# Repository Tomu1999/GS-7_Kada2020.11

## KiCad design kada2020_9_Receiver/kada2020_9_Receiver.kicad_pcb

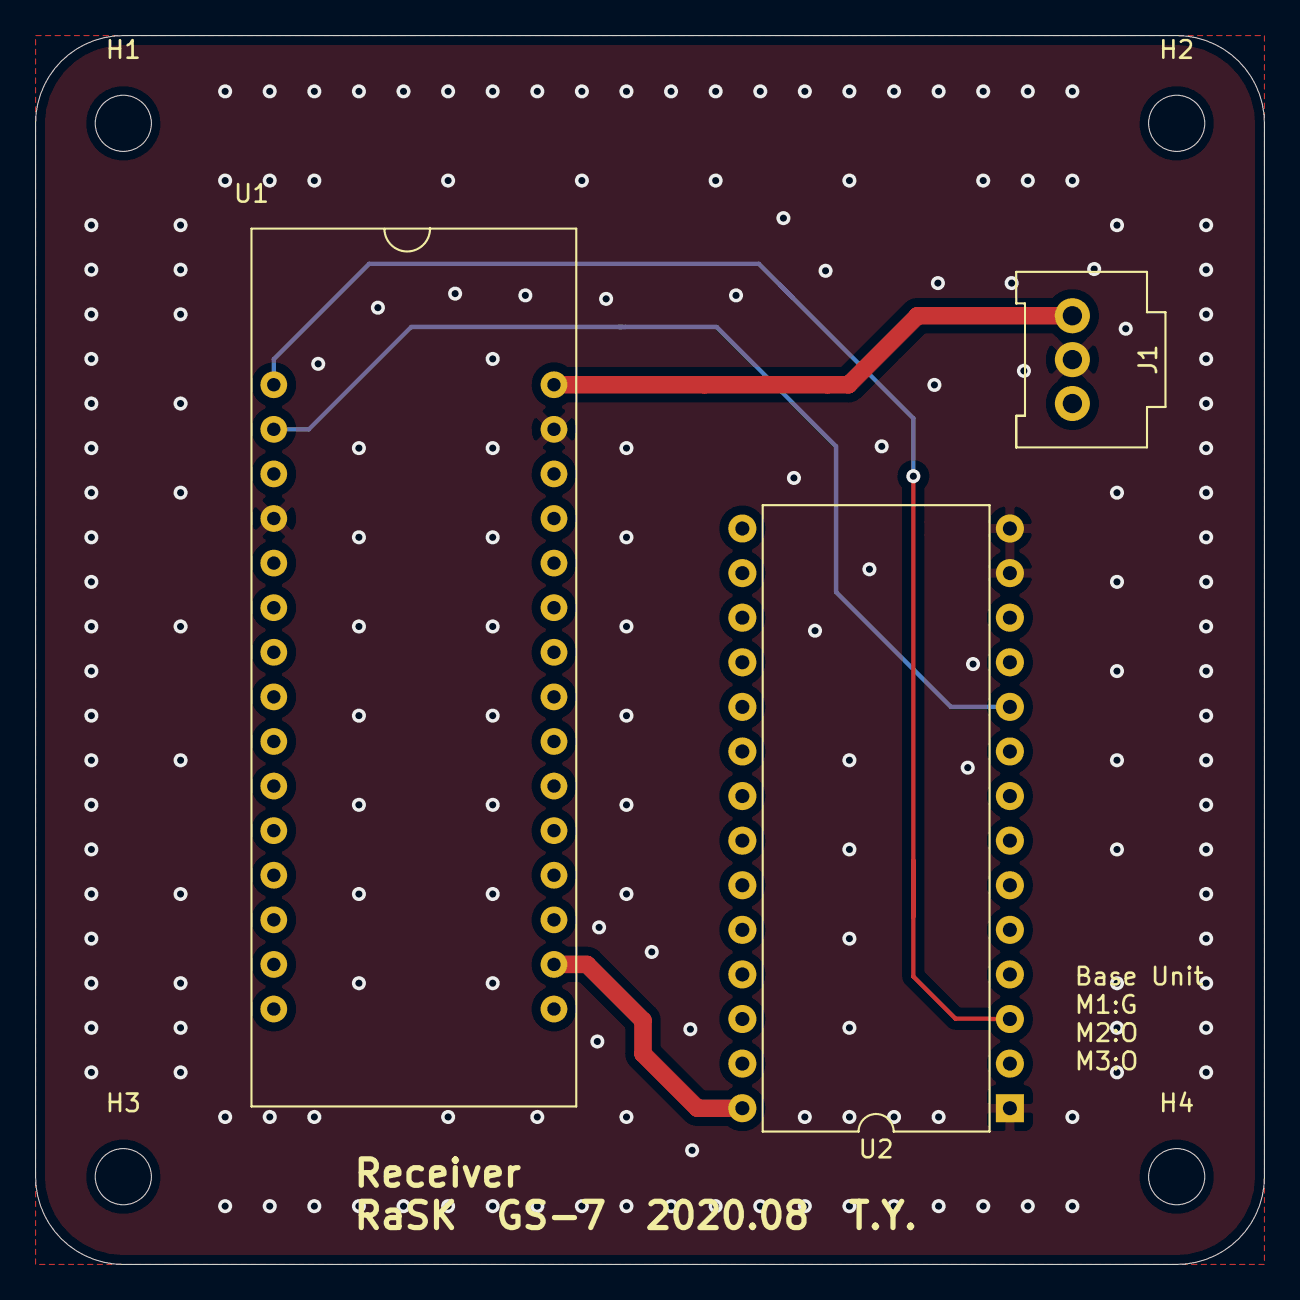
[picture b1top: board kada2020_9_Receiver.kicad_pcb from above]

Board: 2 copper layers, 70.0 x 70.0 mm, 7 parts (0 on the bottom side), 5 nets.

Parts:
H1, H2, H3, H4: MountingHole; MountingHole_3.2mm_M3
J1: 9V; Hirose_DF1E_DF1E-3P-2.5DS_1x03_P2.5mm_Vertical
U1: Nucleo_STM32F303K8; STM32 Nucleo Board STM32F303K8
U2: RF_ZigBee_MW-R-DP-W; DIP-28_W15.24mm

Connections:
+3V3: U1.17, U2.28
+9V: J1.1, U1.30
GND: J1.2, U1.4, U1.29, U2.1, U2.13, U2.14
UART1_RX: U1.2, U2.10
UART1_TX: U1.1, U2.3

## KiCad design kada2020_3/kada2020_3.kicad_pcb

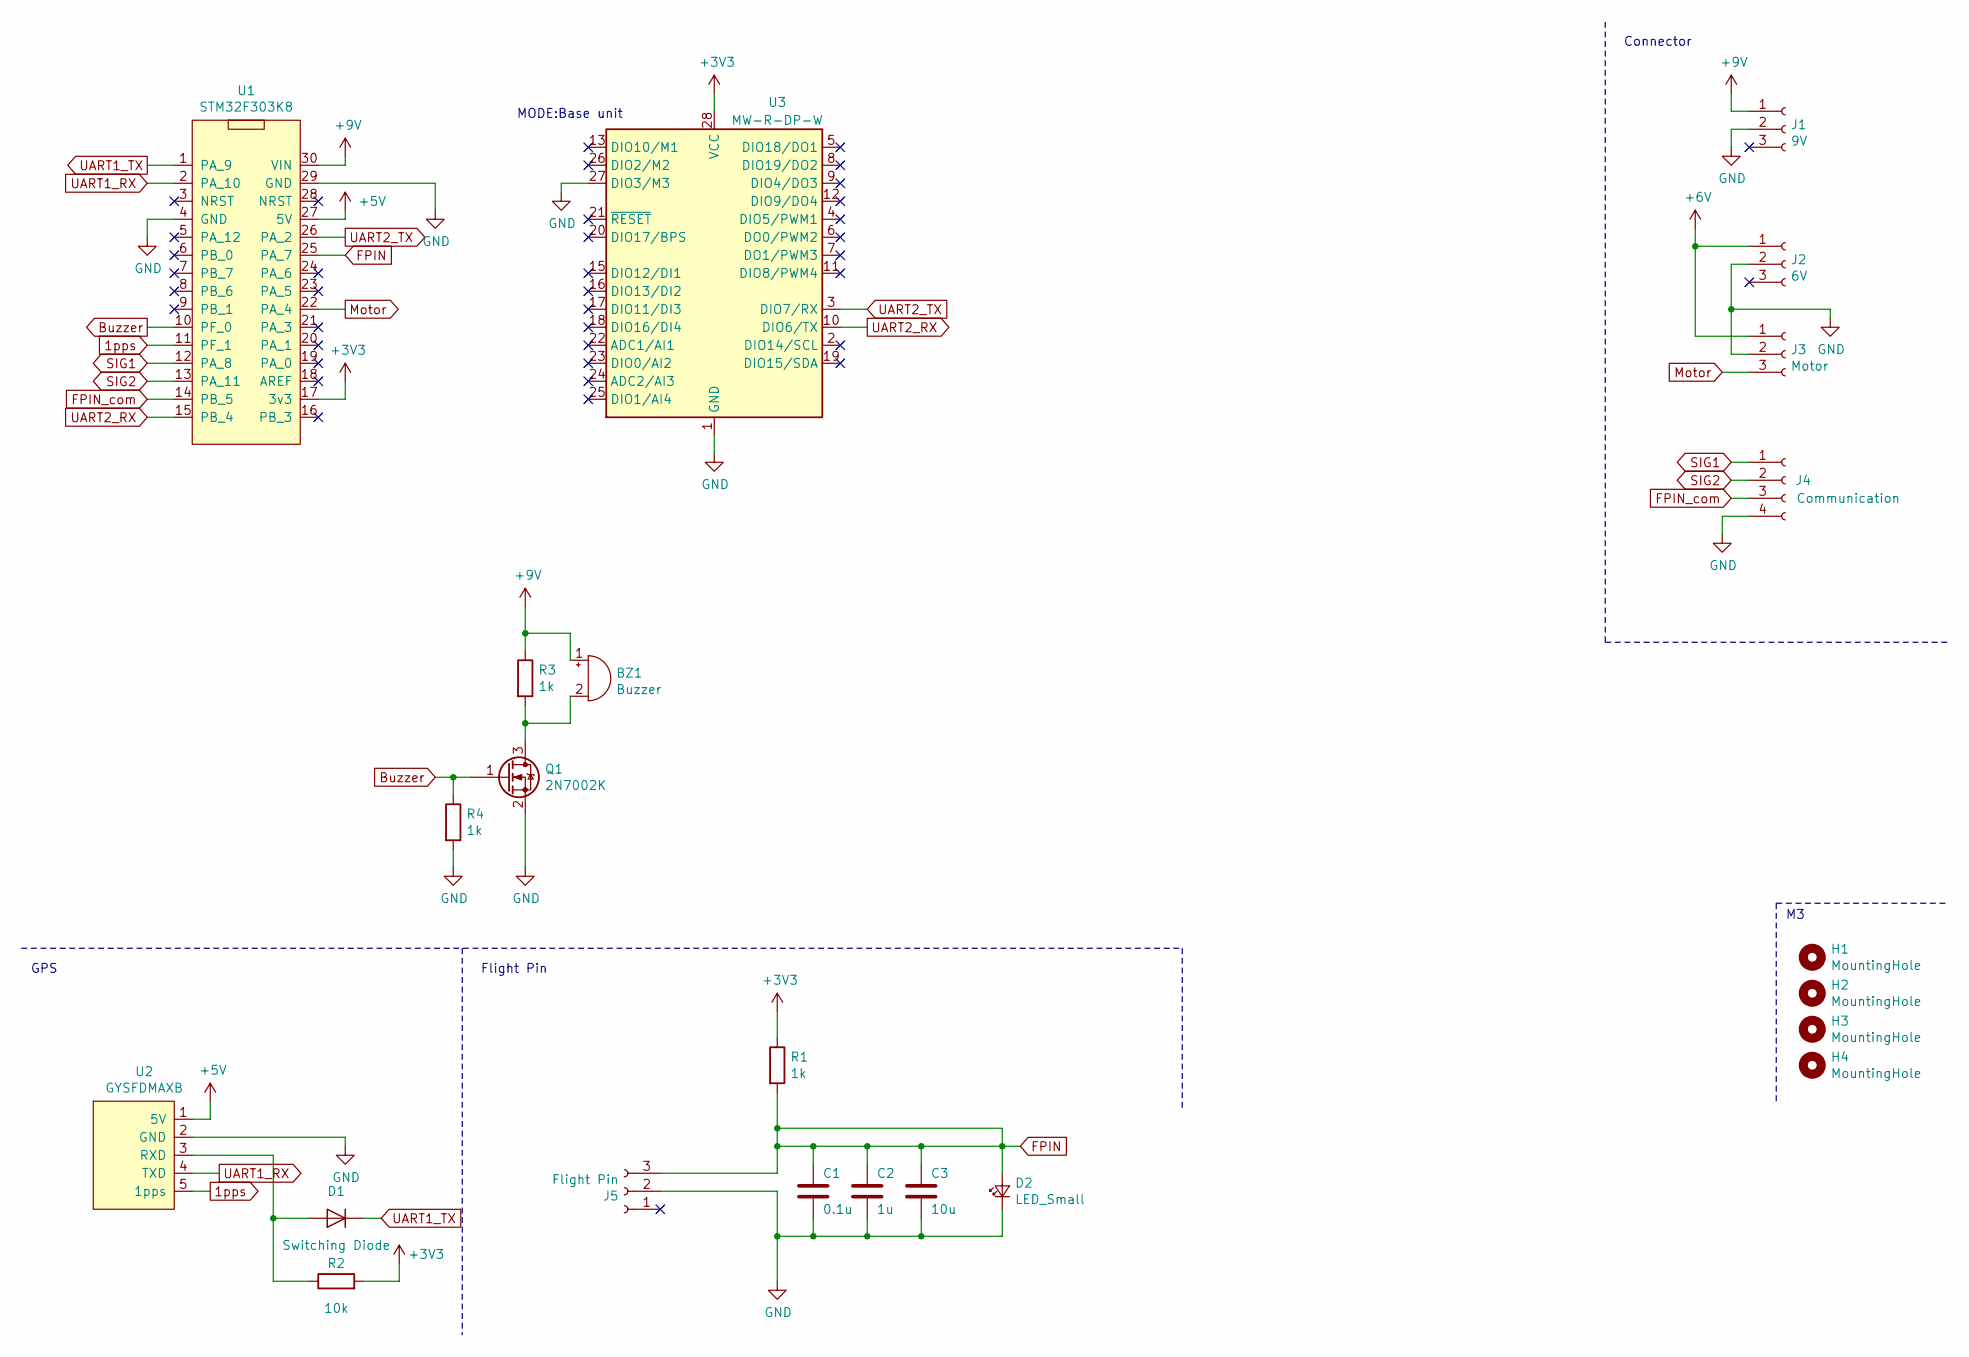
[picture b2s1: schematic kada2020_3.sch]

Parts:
BZ1: Buzzer; Hirose_DF1E_DF1E-3P-2.5DS_1x03_P2.5mm_Vertical
C1: 0.1u; C_0603_1608Metric
C2: 1u; C_0603_1608Metric
C3: 10u; C_0603_1608Metric
D1: Switching Diode; 1N4148W
D2: LED_Small; LED_D3.0mm
H1, H2, H3, H4: MountingHole; MountingHole_3.2mm_M3
J1: 9V; Hirose_DF1E_DF1E-3P-2.5DS_1x03_P2.5mm_Vertical
J2: 6V; Hirose_DF1E_DF1E-3P-2.5DS_1x03_P2.5mm_Vertical
J3: Motor; Hirose_DF1E_DF1E-3P-2.5DS_1x03_P2.5mm_Vertical
J4: Communication; Hirose_DF1E_DF1E-4P-2.5DS_1x04_P2.5mm_Horizontal
J5: Flight Pin; Hirose_DF1E_DF1E-3P-2.5DS_1x03_P2.5mm_Vertical
Q1: 2N7002K; SOT-23
R1, R3: 1k; R_0603_1608Metric
R2: 10k; R_0603_1608Metric
R4: 1k; D_0603_1608Metric
U1: STM32F303K8; STM32 Nucleo Board STM32F303K8
U2: GYSFDMAXB; AE-GYSFDMAXB
U3: MW-R-DP-W; TWELITE-DIP

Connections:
1pps: U1.11 (PF_1), U2.5 (1pps)
+3V3: R1.1, R2.2, U1.17 (3v3), U3.28 (VCC)
+5V: U1.27 (5V), U2.1 (5V)
+6V: J2.1, J3.1
+9V: BZ1.1 (-), J1.1, R3.1, U1.30 (VIN)
Buzzer: Q1.1 (G), R4.1, U1.10 (PF_0)
FPIN: C1.1, C2.1, C3.1, D2.2 (A), J5.3, R1.2, U1.25 (PA_7)
FPIN_com: J4.3, U1.14 (PB_5)
GND: C1.2, C2.2, C3.2, D2.1 (K), J1.2, J2.2, J3.2, J4.4, J5.2, Q1.2 (S), R4.2, U1.4 (GND), U1.29 (GND), U2.2 (GND), U3.1 (GND), U3.14 (GND), U3.27 (DIO3/M3)
Motor: J3.3, U1.22 (PA_4)
unnamed: BZ1.2 (+), Q1.3 (D), R3.2
unnamed: D1.2 (A), R2.1, U2.3 (RXD)
SIG1: J4.1, U1.12 (PA_8)
SIG2: J4.2, U1.13 (PA_11)
UART1_RX: U1.2 (PA_10), U2.4 (TXD)
UART1_TX: D1.1 (K), U1.1 (PA_9)
UART2_RX: U1.15 (PB_4), U3.10 (DIO6/TX)
UART2_TX: U1.26 (PA_2), U3.3 (DIO7/RX)

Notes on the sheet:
GPS
Flight Pin
Connector
MODE:Base unit

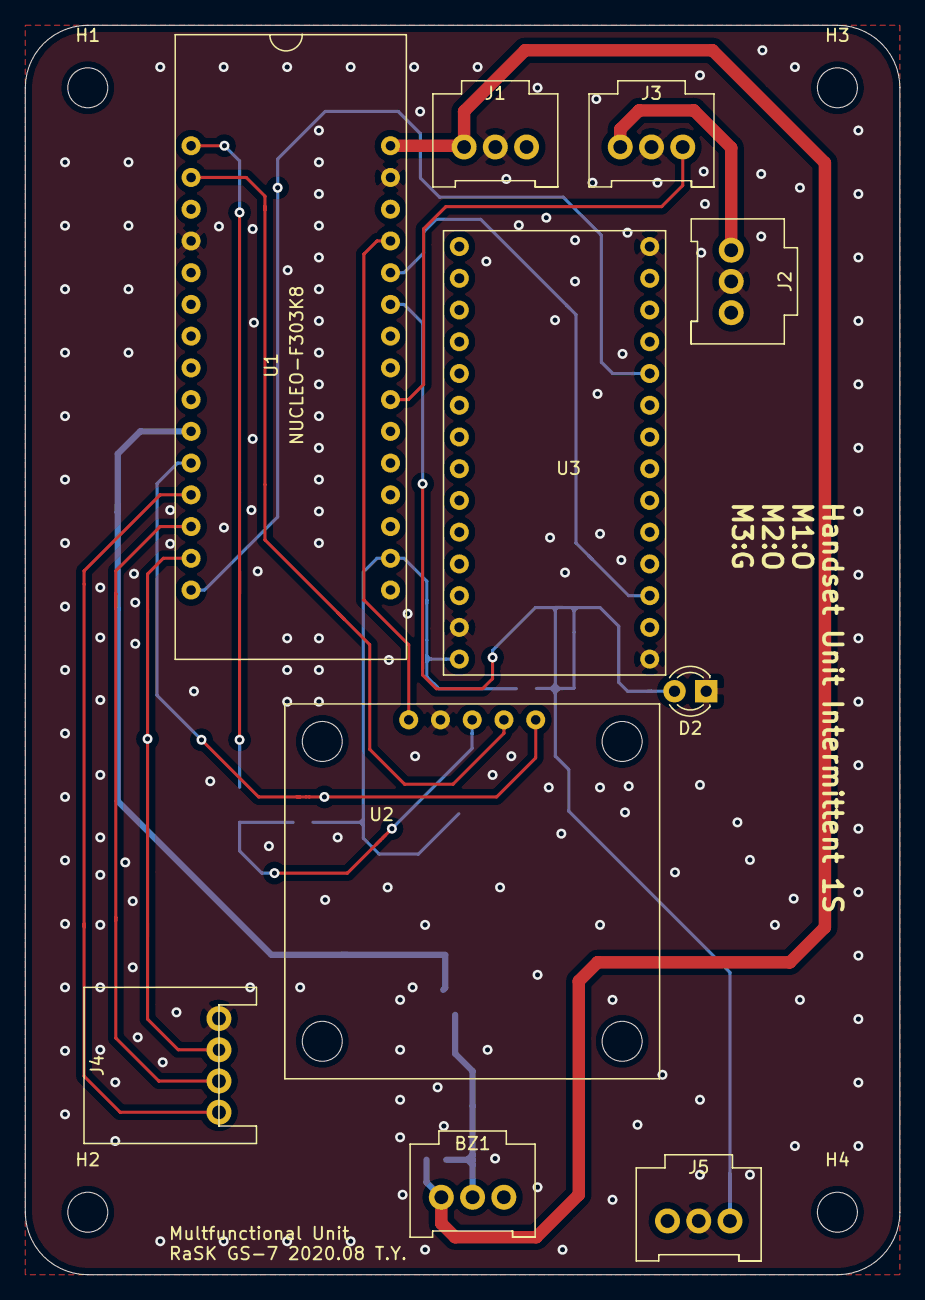
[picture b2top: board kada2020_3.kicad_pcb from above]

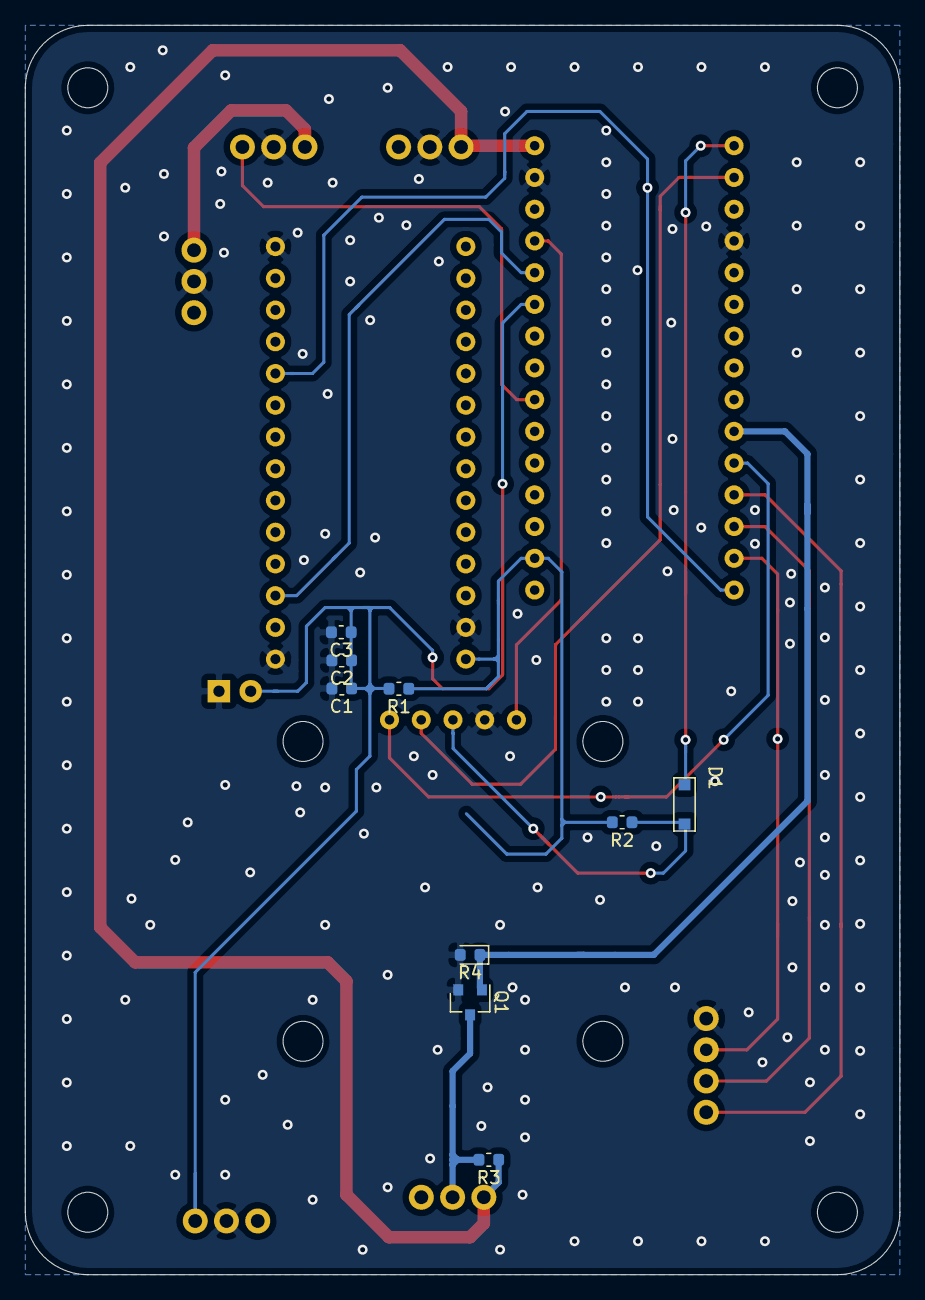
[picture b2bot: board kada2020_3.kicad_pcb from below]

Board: 2 copper layers, 70.0 x 100.0 mm, 23 parts (9 on the bottom side), 18 nets.
